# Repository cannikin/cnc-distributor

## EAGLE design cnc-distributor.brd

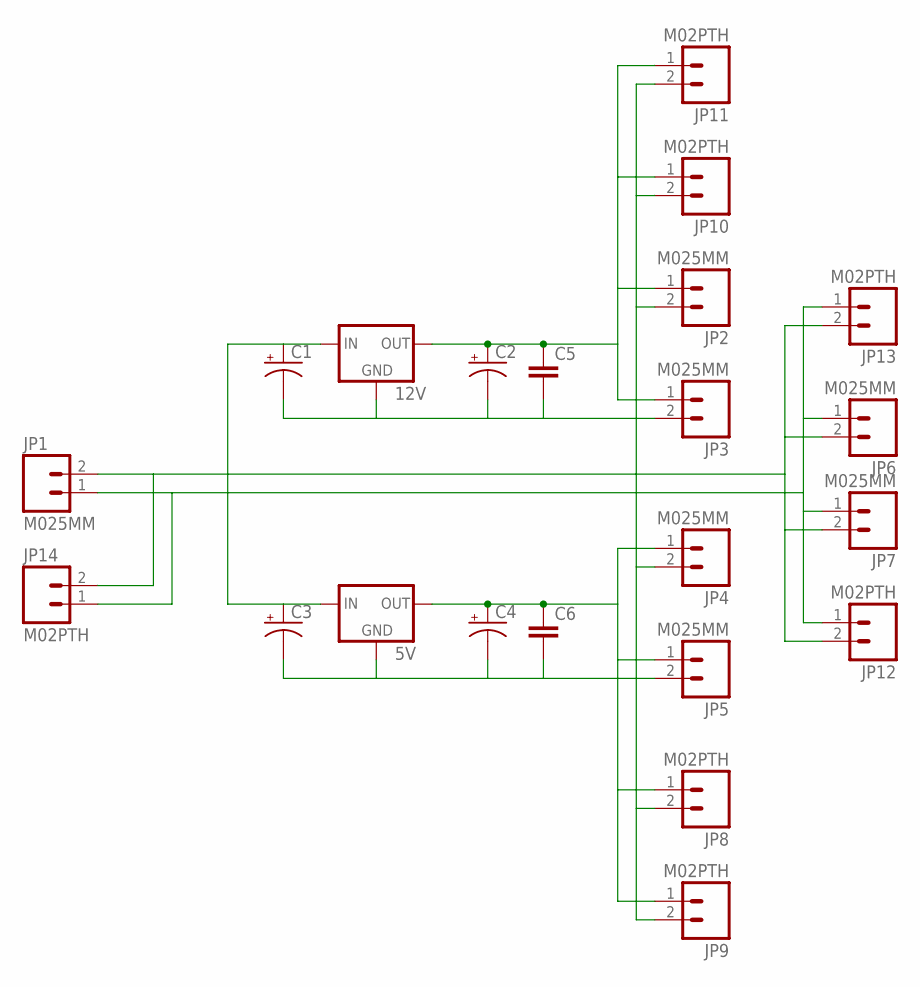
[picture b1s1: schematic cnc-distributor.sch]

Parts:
5V, 12V: 78XXS
C1, C2, C3, C4: CAP_POLPTH2; CPOL-RADIAL-10UF-25V
C5, C6: CAPPTH2; CAP-PTH-SMALL2
JP1, JP2, JP3, JP4, JP5, JP6, JP7: M025MM; SCREWTERMINAL-5MM-2
JP8, JP9, JP10, JP11, JP12, JP13, JP14: M02PTH; 1X02

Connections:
5V: 12V.OUT, C2.1 (+), C5.1, JP2.1, JP3.1, JP10.1, JP11.1
12V: 5V.OUT, C4.1 (+), C6.1, JP4.1, JP5.1, JP8.1, JP9.1
24V: 5V.IN, 12V.IN, C1.1 (+), C3.1 (+), JP1.1, JP6.1, JP7.1, JP12.1, JP13.1, JP14.1
GND: 5V.GND, 12V.GND, C1.2 (-), C2.2 (-), C3.2 (-), C4.2 (-), C5.2, C6.2, JP1.2, JP2.2, JP3.2, JP4.2, JP5.2, JP6.2, JP7.2, JP8.2, JP9.2, JP10.2, JP11.2, JP12.2, JP13.2, JP14.2

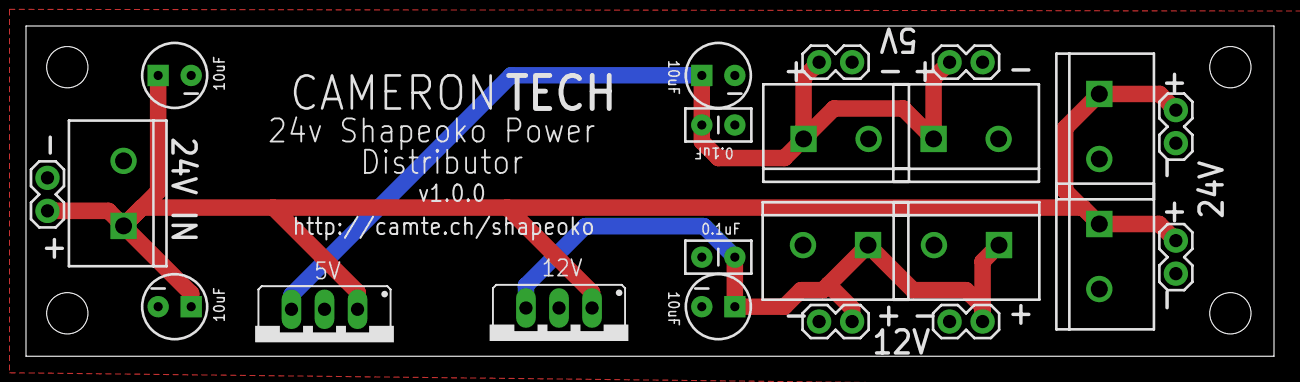
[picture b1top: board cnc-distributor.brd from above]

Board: 2 copper layers, 96.0 x 25.4 mm, 22 parts (0 on the bottom side), 4 nets.

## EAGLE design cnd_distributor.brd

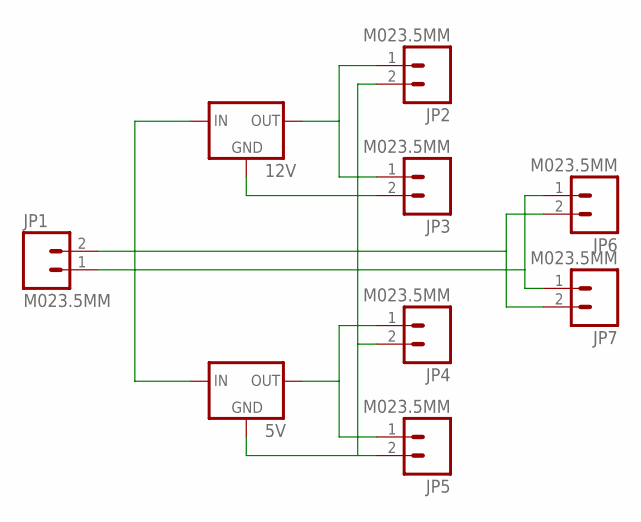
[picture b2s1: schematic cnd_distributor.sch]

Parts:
5V, 12V: 78XXS
JP1, JP2, JP3, JP4, JP5, JP6, JP7: M023.5MM; SCREWTERMINAL-3.5MM-2

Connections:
5V: 12V.OUT, JP2.1, JP3.1
12V: 5V.OUT, JP4.1, JP5.1
24V: 5V.IN, 12V.IN, JP1.1, JP6.1, JP7.1
GND: 5V.GND, 12V.GND, JP1.2, JP2.2, JP3.2, JP4.2, JP5.2, JP6.2, JP7.2

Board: 2 copper layers, 9 parts (0 on the bottom side), 4 nets, no tracks yet.

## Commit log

2014-02-03 Renamed, final version

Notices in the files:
parts and their libraries:
SparkFun-Connectors: Licensing: CC v3.0 Share-Alike You are welcome to use this library for commercial purposes.
